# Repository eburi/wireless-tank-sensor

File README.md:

# 🚤 wireless-tank-sensor

A sealed, potted, maintenance-free **water tank level sensor** for boats (or caravans,
cabins, anything with a resistive tank sender and a 12 V bus). It runs on a
**Seeed XIAO ESP32-C3**, measures the plain old resistive float sender, works out the
level itself, and shouts the result at **Home Assistant** over **Bluetooth (BTHome v2)**.

You run **two wires** (12 V and ground) to the tank. That's it. No gauge, no Wi-Fi at
the tank, no app, no cloud. Everything else happens in the Home Assistant box you
already have on board.

> **TL;DR** — three ESPHome [external components](https://esphome.io/components/external_components/)
> (`bthome_beacon`, `tank_level`, `ota_beacon`) plus ready-to-copy example configs.
> Read on for the story, the wiring, and the lessons that cost me a night of sleep.

---

## 🧭 The backstory

When I bought the boat, she came with a set of tank sensors and a very confident
ship's manual. What she did *not* come with were the **analog gauges** those sensors
once fed — a previous owner had removed them at some point in the last geological era,
leaving behind a few dangling wires, a hole in the panel, and a gap in my
understanding of how much fresh water was actually left.

So for the first seasons the "fresh water level" was determined by a highly advanced
algorithm: *the pump starts sounding sad → tank is empty*. This works, in the sense
that a smoke alarm "works" as an oven timer.

Eventually I ripped out the corroded old senders and dropped in **cheap standard
resistive float senders** (~10 Ω to ~180 Ω, the kind every chandlery sells for the
price of a round of drinks). Then came the question: what to connect them to? Buying
new analog gauges felt like installing a fax machine. Buying a "smart" marine tank
monitor felt like paying for a fax machine with a subscription.

Meanwhile there was already a **Home Assistant** box on board, quietly collecting
temperatures, battery voltages and GPS fixes. It has Bluetooth. Bluetooth reaches the
tank locker. You can see where this is going.

The result is this repo: a tiny board that sits by the tank, needs only 12 V, sleeps
almost all the time, wakes up every ten seconds to measure the sender, and broadcasts
the level as a BTHome advertisement. Home Assistant picks it up like any other BTHome
gadget — no pairing, no integration to install, no IP address. The Wi-Fi radio is
switched off and only wakes for firmware updates, because on a boat the Wi-Fi is the
first thing you turn off to save power.

Now the fresh water tank shows up on the dashboard next to the batteries, the "tank
almost empty" sensor can nag me on my phone, and the pump has stopped sounding sad
unexpectedly. Mostly.

---

## ✨ What it does

| | |
|---|---|
| 📡 **BTHome v2 over BLE** | Home Assistant auto-discovers the sensor. Level (%), volume (L), raw sender resistance (Ω) and an *almost empty* problem flag, all in one 31-byte advertisement. |
| 😴 **Deep sleep duty cycle** | Wake → power the measurement chain → sample for ~2.5 s → advertise → sleep 10 s. The sender, the INA238 and its LED are completely unpowered in between. |
| 🧠 **Self-calibrating** | Learns the sender's real min/max resistance from the tank being filled and drained. Conservative: a new extreme needs five spaced observations, the least extreme one wins, the range never shrinks, spikes decay. Persisted to flash. |
| 🪣 **Tank content model** | Float senders have a dead zone at the bottom. Tell it total litres and how many litres the pump still delivers after the gauge reads 0 %, and it reports true content + a "you are now drinking the reserve" flag. Both numbers are editable in HA and stored on the device. |
| 🔒 **Wi-Fi off by default** | Turned on only in a 5-minute *maintenance window*: after a power cycle, or on request via a BLE trigger. If the boat Wi-Fi is gone, the node opens a fallback access point with a captive portal instead. |
| 🛰️ **BLE-triggered OTA** | A second ESP32 by the HA box advertises an iBeacon on demand (an HA switch). The sleeping sensor hears it on its next wake, opens Wi-Fi, and you flash it from the ESPHome dashboard. Potted in resin? Doesn't matter. |
| 🧱 **Fleet friendly** | One shared package, one ten-line file per tank, per-tank OTA targets, one API key for all. |
| 🔌 **Two wires** | 12 V in. Level out, through the air. |

---

## 🏗️ How it works

```mermaid
flowchart LR
    BUS[12 V bus] -->|PTC fuse, TVS, reverse diode| BUCK[buck module<br/>3.3 V]
    BUCK --> XIAO[XIAO ESP32-C3]
    XIAO <-->|I2C| INA[INA238<br/>current + voltage]
    RAIL[3.3 V] --> INA --> R2[series resistor] --> SENDER[float sender<br/>10–180 Ω] --> FET[logic-level MOSFET<br/>low-side switch] --> GND
    XIAO -->|GPIO3 MEAS_EN| FET
    XIAO -.->|BTHome adverts| HA[Home Assistant<br/>Bluetooth]
    BEACON[OTA trigger node<br/>second ESP32] -.->|iBeacon on demand| XIAO
    HA -->|switch| BEACON
```

The sender is just a variable resistor. The ESP switches a small current through it,
the INA238 measures that current and the voltage across the sender, and
`R = V / I`. No dependence on the supply rail, no dependence on the series resistor,
no ADC calibration. The `tank_level` component turns resistance into a percentage
using what it has learned about *your* sender, and `bthome_beacon` packs it into a
BTHome advertisement.

Because the node only listens for the OTA trigger while it is awake anyway, the
trigger costs nothing extra in power, and because it is a standard iBeacon frame
Home Assistant's iBeacon integration even shows the trigger as "present" while it is
on air — free proof the transmitter is transmitting.

---

## 🔩 Hardware

Two ways to build it. Both run the same firmware and the same example configs.

### Rev 3 — the carrier PCB (recommended)

A **55 × 52 mm four-layer carrier** in [hardware/kali-tank-sensor-v3/](hardware/kali-tank-sensor-v3/):
KiCad 10 project, DRC/ERC clean, gerbers, drill files, pick-and-place and BOM, ready for
a PCBWay-style order with SMT assembly. The XIAO and the buck module are hand-soldered
on top afterwards; four wire pads with strain-relief holes take the harness. See
[FABRICATION.md](hardware/kali-tank-sensor-v3/FABRICATION.md) for the order parameters,
assembly order and the things to check before first power-up.

| Part | Role | Approx. cost |
|------|------|-------------:|
| Seeed **XIAO ESP32-C3** + its **U.FL antenna** | Brain, BLE, deep sleep | €6 |
| **INA238** (bare MSOP-10, PCBWay places it) + **1 Ω 0.1 %** shunt | Measures chain current and sender voltage | €3 |
| **AO3400A** logic-level MOSFET | Low-side switch: sender is only powered while measuring | €0.10 |
| 100 Ω, 100 Ω, 100 kΩ, 2 × 4.7 kΩ | Current limit, gate series, gate pull-down, I2C pull-ups | pennies |
| 5–30 V → **3.3 V** buck module, 18 × 12 mm (mikroshop #2835 / DSN-MINI-360 class) | 12 V → 3.3 V | €1 |
| SS34, SMBJ16A, 200 mA PTC, 2 × 22 µF, 2 × 100 nF | Reverse-polarity, TVS, fuse, rail buffering | €1 |
| A resistive tank sender (any 10–180 Ω / 240–33 Ω / 0–190 Ω float sender) | The thing in the tank | €15–40 |

The whole thing runs on one 3.3 V rail: the buck feeds the XIAO's 3V3 pad through a
solder bridge (open it before plugging in USB), and the measurement chain runs from the
same rail through the INA238's own 1 Ω shunt. The I2C pull-ups hang on the switched
INA238 supply, so nothing back-feeds the chip while it sleeps unpowered.

### Rev 2 — the breadboard build

What ran on the bench and on the boat first: an INA238 *breakout* with its 15 mΩ shunt,
a BS170, a MINI-360 set to 5 V. Still valid, and the full wiring schema, part rationale,
bench findings and power budget for it live in [docs/hardware.md](docs/hardware.md).

| Part | Role | Approx. cost |
|------|------|-------------:|
| Seeed **XIAO ESP32-C3** + its **U.FL antenna** | Brain, BLE, deep sleep | €6 |
| **INA238** breakout (with onboard 15 mΩ shunt, I2C addr 0x40) | Measures chain current and sender voltage | €4 |
| **BS170** N-channel MOSFET | Low-side switch: sender is only powered while measuring | €0.20 |
| 150 Ω ¼ W, 100 Ω, 100 kΩ | Current limit, gate series, gate pull-down | pennies |
| **MINI-360** buck converter (set to 5.0 V) | 12 V → 5 V | €1 |
| 470 µF / 10 V, Schottky (1N5817), fuse | Rail buffering, USB back-feed protection, 12 V protection | €1 |

### XIAO pins (both revisions)

| XIAO pin | GPIO | Goes to |
|----------|------|---------|
| 3V3 (rev 3) / 5V (rev 2) | — | Supply from the buck; rev 3 via solder bridge SB1 |
| GND | — | Common ground |
| D1 | GPIO3 | MOSFET gate via 100 Ω (`MEAS_EN`) |
| D4 | GPIO6 | INA238 SDA |
| D5 | GPIO7 | INA238 SCL |
| D10 | GPIO10 | INA238 supply (`VS`, switched — the chip and its pull-ups are off in deep sleep) |

The sender must be **two-wire / isolated** (both terminals free) for the low-side
switch to work. A hull-grounded single-wire sender needs high-side switching instead —
adapt the FET stage, the firmware doesn't care.

---

## 🚀 Installing

You need ESPHome (the Home Assistant add-on is fine) and a Home Assistant with a
Bluetooth adapter or an ESPHome Bluetooth proxy in range of the tank.

### 1. Grab the example configs

Copy the [`examples/`](examples/) folder into your ESPHome config directory:

```
esphome/
  packages/tank-common.yaml     everything shared: sensors, INA238, tank_level, BTHome, HA numbers
  packages/tank-sleep.yaml      the sleep cycle + BLE trigger matcher (includes tank-common)
  water-tank-1.yaml             one device file per tank — copy it for tank 2, 3, …
  water-tank-bench.yaml         same hardware, Wi-Fi always on, no sleep: for first hookup
  ota-trigger-beacon.yaml       the trigger node (second ESP32, lives next to HA)
  secrets.yaml.example          copy to secrets.yaml and fill in
```

The components are pulled straight from this repo:

```yaml
external_components:
  - source: github://eburi/wireless-tank-sensor
    components: [bthome_beacon, tank_level]   # the trigger node uses [ota_beacon]
    refresh: 1d
```

Pin to a release for reproducible builds: `source: github://eburi/wireless-tank-sensor@v1.0.0`.

### 2. Name your tank

A device file is four lines of substitutions and one include:

```yaml
substitutions:
  device_name: water-tank-1       # ESPHome node name / hostname
  friendly_name: "Water Tank 1"   # prefix of every HA entity
  bthome_name: Tank1              # BLE local name, max 9 characters (the advert is full)
  ota_target: "1"                 # 1–255, unique per tank — which OTA trigger it answers to

packages:
  sleep: !include packages/tank-sleep.yaml
```

### 3. Check the sender direction

`tank_level` maps **low resistance = empty** by default. Many European / VDO-style
senders are the other way round (~10 Ω full, ~180 Ω empty). If your gauge goes down
while you fill, set `invert: true` in `packages/tank-common.yaml`. (Or just look at the
learned-range sensors while filling; it becomes obvious very quickly.)

### 4. Flash and forget

1. Flash **`water-tank-bench.yaml`** first, over USB. It keeps Wi-Fi on and the
   measurement chain powered, so you can watch *Sender resistance*, *Chain current*
   and *Sender voltage* live and confirm the wiring before you pot anything.
2. Once the numbers make sense, OTA-flash **`water-tank-1.yaml`**. From now on the
   node sleeps and only advertises over BLE.
3. Home Assistant → *Settings → Devices & Services* will offer a new **BTHome** device
   called `Tank1`. Accept it. Done.

### 5. Let it learn, then tell it about litres

Calibration happens by itself: fill the tank, empty the tank, repeat a couple of times
over the season. The learned range shows up as **Learned R min / max** and is saved to
flash, so it survives power cuts and firmware updates.

For real litres, do the **pump test** once: drain until the level reads its floor, then
count the litres the pump still delivers until it starts gasping. Enter that as
**Tank reserve volume** and the tank capacity as **Tank total volume** — two `number`
entities on the ESPHome device in HA (visible while the maintenance window is open; they
are stored on the ESP). From then on the level is true content and **Tank volume** reports
litres.

---

## 🏠 What shows up in Home Assistant

Via **BTHome** (always, over Bluetooth, no Wi-Fi involved):

| Entity | BTHome object | Meaning |
|--------|---------------|---------|
| `sensor.tank1_moisture` (HA may add a MAC suffix) | moisture (%) | Tank level. Yes, "moisture" — BTHome has no "tank level" object and moisture is a percentage. Rename it, nobody will know. |
| `sensor.tank1_volume` | volume (0.1 L) | Litres in the tank, once total/reserve are set |
| `sensor.tank1_count` | count (uint16) | Raw sender resistance × 10 (diagnostic; 1234 = 123.4 Ω) |
| `binary_sensor.tank1_problem` | problem | **Almost empty** — float on its bottom stop, you're drinking the reserve |

Via the **ESPHome native API** (only while Wi-Fi is on, i.e. in the maintenance window
or on the bench variant): the raw INA238 readings, *Sender resistance*, *Learned R min /
max*, the *Measurement path* and *INA238 power* switches, and the two litre `number`s.

---

## 🛰️ Updating firmware without touching the thing

The sensor is meant to be potted in resin inside a locker you never want to open
again, so it must be updatable without physical access — but it also keeps Wi-Fi off.
Two ways in:

- **Power cycle.** A cold boot always opens a **5-minute maintenance window**: Wi-Fi on,
  API on, continuous measurement. Flash from the ESPHome dashboard inside that window.
- **BLE trigger.** Flash a second ESP32 with [`ota-trigger-beacon.yaml`](examples/ota-trigger-beacon.yaml)
  and park it near the HA box. It exposes one HA switch per tank (**OTA trigger tank 1**,
  **… tank 2**, **… all tanks**). Turn one on: it advertises an iBeacon for 4 minutes,
  the matching sensor hears it on its next wake, opens its maintenance window, and you
  flash it. The switch turns itself off; a 6-minute firmware backstop makes sure the
  beacon never advertises forever (which would make every sensor open Wi-Fi on every
  wake — that's why ESPHome's built-in `esp32_ble_beacon` couldn't be used: it has no
  runtime off switch).

- **No Wi-Fi at all?** Every example carries a fallback **access point + captive portal**.
  If a node cannot join the configured Wi-Fi within a minute of switching the radio on, it
  opens a WPA2 access point named after the device (`water-tank-1`, …), protected by
  `wifi_ap_password` from `secrets.yaml`. Join it, and the captive
  portal lets you enter new credentials or upload a firmware file — still no screwdriver.

> **Why not transmit from the HA host's own Bluetooth?** Tried it. On Home Assistant OS
> the Bluetooth integration owns the adapters and BlueZ refuses to register an
> advertisement (`org.bluez.Error.Failed`), even on an idle second adapter. A €6 ESP32 is
> cheaper than fighting BlueZ, and it doubles as a Bluetooth proxy.

> **The trigger format is a contract between two firmwares.** If you change the UUID,
> major or minor, reflash *both* ends. A sensor on an old build silently ignores the new
> trigger, and you will spend an evening wondering why. Ask me how I know.

---

## 🧪 The components

All three are plain ESPHome external components under [`components/`](components/).

### `bthome_beacon`

Non-connectable BLE advertiser producing a BTHome v2 service-data frame (UUID `0xFCD2`).
Objects are emitted in ascending id order as BTHome requires: packet id, `almost_empty`
(problem, `0x26`), `level` (moisture, `0x2F`), `count` (`0x3D`, value × 10), `volume`
(`0x47`, 0.1 L). Re-advertises once per second with the current sensor states.

```yaml
bthome_beacon:
  device_name: "Tank1"          # ≤ 9 chars if all four objects are used
  level: tank_level_cal         # sensor, % (required)
  count: sender_resistance      # sensor, × 10 → uint16 (optional)
  volume: tank_volume           # sensor, L (optional)
  almost_empty: tank_almost_empty   # binary_sensor (optional)
```

### `tank_level`

Resistance in, level out. Median-of-5 input window (kept in RTC memory so it spans
wake cycles), conservative learned min/max with NVS persistence that only ever learns
from a full-window median, EMA smoothing across deep-sleep cycles, and implausible
readings (outside `plausible_min`/`plausible_max`, NaN) hold the last good level
instead of publishing garbage. Optional volume model.

```yaml
tank_level:
  id: tank_model
  source: sender_resistance     # raw Ω sensor
  seed_min: 3.0                 # assumed range until enough is learned
  seed_max: 183.0
  invert: false                 # true if low resistance = full
  plausible_max: 250            # Ω; readings above are faults (default 400)
  level: { name: "Tank level" }
  volume: { name: "Tank volume" }
  almost_empty: { name: "Tank almost empty" }
  learned_min: { name: "Learned R min" }
  learned_max: { name: "Learned R max" }
```

Runtime setters `set_total_volume(l)` / `set_reserve_volume(l)` are what the two HA
`number` entities in the example call, and `reset_calibration()` is behind the
**Reset calibration** button: the learned range never shrinks on its own, so press it
after swapping the sender or whenever a bad range got in, then move the float through
its full travel a few times.

### `ota_beacon`

iBeacon transmitter with a runtime on/off and a safety timeout. Fixed major `0x4B4F`
("KO"), minor `0x54<target>` ("T" + tank number, 0 = all tanks). The sensor matches on
major/minor because those are byte-order unambiguous in ESPHome's iBeacon parser; the
UUID is only for Home Assistant's iBeacon integration to display.

```yaml
ota_beacon:
  id: trigger
  uuid: c0a1b2c3-d4e5-4f60-8172-8394a5b6c7d8
  safety_timeout: 6min
# then from a switch/automation:  id(trigger).start(1);  id(trigger).stop();
```

---

## 🧯 Lessons learned (so you don't have to)

- **The XIAO ESP32-C3 has no on-board antenna.** None. The U.FL pigtail is not optional.
  Without it the radio still "works" at bench range — BTHome reached a Raspberry Pi two
  metres away at −98 dBm, one dB above the noise floor — which is exactly why it went
  unnoticed while I debugged the OTA trigger firmware on *both* ends for a whole night.
  Attaching the antenna took the signal to a healthy −75 dBm. Glue the antenna down
  before potting; the connector pops off.
- **Check your MOSFET pinout with a meter.** My batch of "BS170"s had a mirrored
  S-G-D pinout. Installed per datasheet they conduct permanently through the body diode.
  The *path-off ≈ 0 mA* check on the bench catches this in ten seconds.
- **INA238 conversion time must fit the update interval.** `adc_time × averaging × 3
  channels` longer than `update_interval` means ESPHome's driver restarts the conversion
  every cycle and never publishes a value. 1052 µs × 128 at 1 s works; 4120 µs × 128
  does not.
- **The breakout's I2C pull-ups ride on its VIN.** At 5 V they idle at 5 V, which the
  ESP32-C3 does not appreciate. Feeding the breakout's VIN from a 3.3 V GPIO fixes the
  levels *and* makes the whole breakout (LED included) switch off in deep sleep for free.
- **Float senders have a dead zone.** The float bottoms out with litres still in the
  tank. Measure it once with the pump, tell the firmware, and stop lying to yourself
  about "0 %".
- **The first sample after switching the sender on is a lie.** The INA238 converts bus
  voltage and shunt current one after the other. Switch the measurement path on between
  the two and you get the resting rail voltage divided by the real current: sender plus
  about 130 Ω. On a sleeping node that happens at the same instant every wake, and the
  calibration happily learned 300 Ω as "full" from five of those. Hence the two-second
  settle gate in the example config, the full-window rule in `tank_level`, and the
  `plausible_max` option.
- **Verify a module's pad map against a photo of its bottom face, not its silkscreen
  logic.** The first carrier footprint grouped the buck's four corner pads by polarity
  (IN+ and IN− at opposite ends). The real module groups them by side: the long pitch
  separates IN from OUT, the short pitch separates + from −. Built as drawn it would have
  put 12 V backwards across the input and shorted the output to ground. Two photos and a
  meter, before ordering, are cheaper than five dead boards.
- **The first board layout is a third empty.** Rev 3.0 came out at 80 × 55 mm because the
  input chain and the buck formed one long row with the MCU beside it. Stacking the buck
  over the MCU and moving the analog block next to the wire pads gave 55 × 52 mm with the
  same circuit and shorter sender traces. Look at the empty regions before you order.
- **A 31-byte advertisement fills up fast.** Four BTHome objects plus a name leave nine
  characters for the name. Keep it short.

---

## 🗂️ Repo layout

```
components/
  bthome_beacon/    BTHome v2 advertiser
  tank_level/       self-calibrating level + volume model
  ota_beacon/       switchable iBeacon OTA trigger
examples/           ready-to-copy ESPHome configs (see Installing)
hardware/
  kali-tank-sensor-v3/  rev 3 carrier PCB: KiCad 10 project, gen_sch.py / gen_pcb.py
                        (the board is generated from source), gerbers + drill + CPL + BOM,
                        FABRICATION.md with order parameters and pre-power-up checks
docs/
  hardware.md       full hardware plan, wiring, rationale, bench notes, power budget
  wiring-schema.svg
  concept.md        the original design brief
.github/workflows/  CI compiles every example against the components in the repo
```

---

## 🤝 Contributing

Issues and PRs welcome — especially reports of other senders, other boards, or a
cleverer way to get litres out of a float. If you build one, I'd love a photo of your
tank locker. Fair winds.

## 📜 License

[MIT](LICENSE). Built for the sailing yacht *Kali*; no boats were harmed in the making
of this firmware, though one MOSFET was.

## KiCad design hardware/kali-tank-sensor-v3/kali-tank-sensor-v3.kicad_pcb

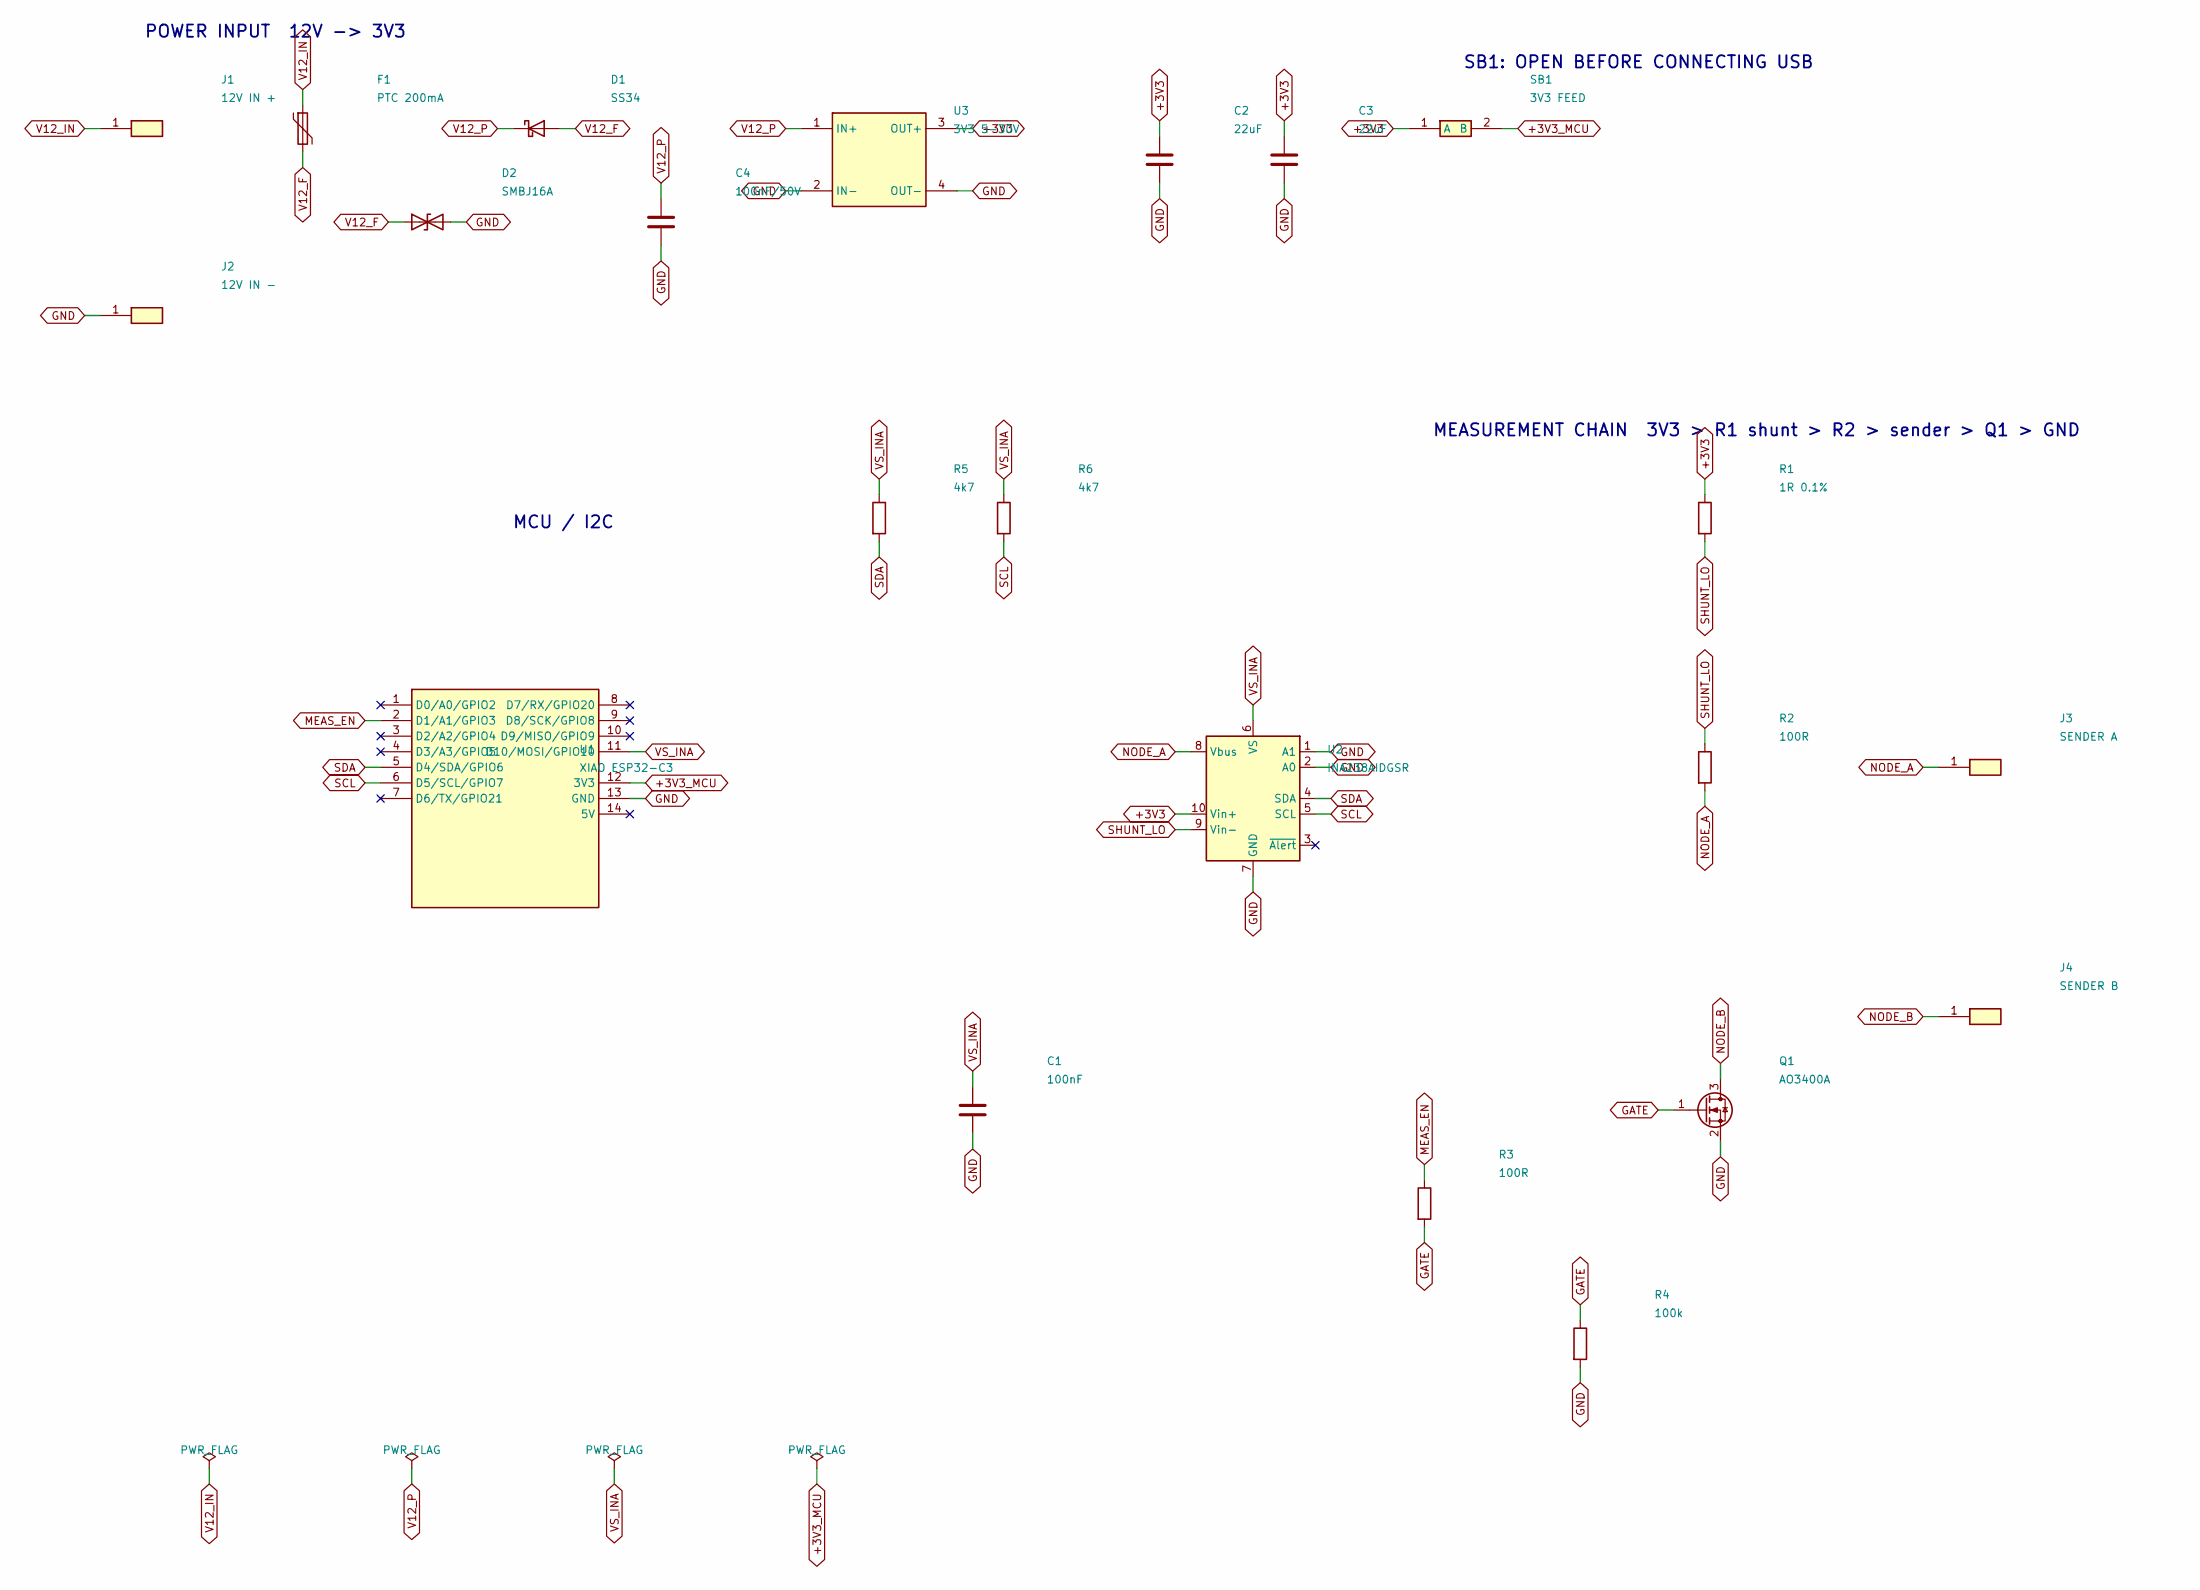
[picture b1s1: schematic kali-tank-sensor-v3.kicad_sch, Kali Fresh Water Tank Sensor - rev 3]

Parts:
C1: 100nF; C_0805_2012Metric
C2, C3: 22uF; C_1206_3216Metric
C4: 100nF/50V; C_0805_2012Metric
D1: SS34; D_SMA
D2: SMBJ16A; D_SMB
F1: PTC 200mA; R_1206_3216Metric
J1: 12V IN +; WirePad_StrainRelief
J2: 12V IN -; WirePad_StrainRelief
J3: SENDER A; WirePad_StrainRelief
J4: SENDER B; WirePad_StrainRelief
Q1: AO3400A; SOT-23
R1: 1R 0.1%; R_0805_2012Metric
R2, R3: 100R; R_0805_2012Metric
R4: 100k; R_0805_2012Metric
R5, R6: 4k7; R_0805_2012Metric
SB1: 3V3 FEED; SolderBridge_2pad
U1: XIAO ESP32-C3; XIAO-ESP32C3_TopSolder
U2: INA238AIDGSR; MSOP-10_3x3mm_P0.5mm
U3: 3V3 5-30V; DCDC_Module_18x12_4pad

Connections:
+3V3: C2.1, C3.1, R1.1, SB1.1 (A), U2.10 (Vin+), U3.3 (OUT+)
+3V3_MCU: SB1.2 (B), U1.12 (3V3)
GATE: Q1.1 (G), R3.2, R4.1
GND: C1.2, C2.2, C3.2, C4.2, D2.2 (A2), J2.1, Q1.2 (S), R4.2, U1.13 (GND), U2.1 (A1), U2.2 (A0), U2.7 (GND), U3.2 (IN-), U3.4 (OUT-)
MEAS_EN: R3.1, U1.2 (D1/A1/GPIO3)
NODE_A: J3.1, R2.2, U2.8 (Vbus)
NODE_B: J4.1, Q1.3 (D)
SCL: R6.2, U1.6 (D5/SCL/GPIO7), U2.5 (SCL)
SDA: R5.2, U1.5 (D4/SDA/GPIO6), U2.4 (SDA)
SHUNT_LO: R1.2, R2.1, U2.9 (Vin-)
V12_F: D1.2 (A), D2.1 (A1), F1.2
V12_IN: F1.1, J1.1
V12_P: C4.1, D1.1 (K), U3.1 (IN+)
VS_INA: C1.1, R5.1, R6.1, U1.11 (D10/MOSI/GPIO10), U2.6 (VS)

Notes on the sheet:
POWER INPUT 12V -> 3V3
MEASUREMENT CHAIN 3V3 > R1 shunt > R2 > sender > Q1 > GND
MCU / I2C
SB1: OPEN BEFORE CONNECTING USB

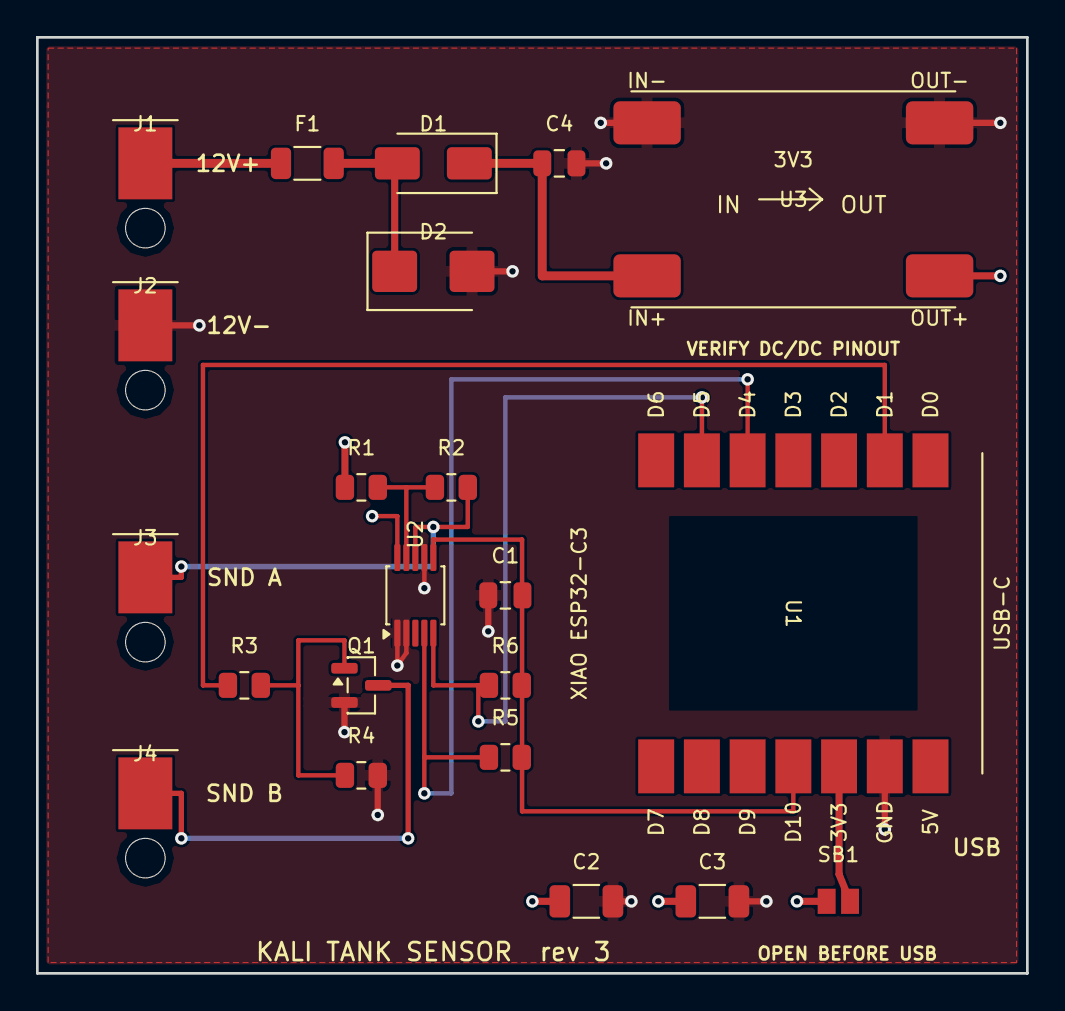
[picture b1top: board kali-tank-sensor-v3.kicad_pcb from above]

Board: 4 copper layers, 55.0 x 52.0 mm, 22 parts (0 on the bottom side), 14 nets.

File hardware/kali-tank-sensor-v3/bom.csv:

Reference,Qty,Value,Footprint,Manufacturer PN,Source,Notes
U1,1,Seeed XIAO ESP32-C3,kali:XIAO-ESP32C3_TopSolder,113991054,Seeed,HAND-SOLDER after delivery. Flash BEFORE soldering down.
U2,1,INA238AIDGSR,Package_SO:MSOP-10_3x3mm_P0.5mm,INA238AIDGSR,LCSC C2868250 / DigiKey,PCBWay places. Consign to avoid markup.
U3,1,3.3V buck 5-30V 3A,kali:DCDC_Module_18x12_4pad,mikroshop 2835,mikroshop.ch,HAND-SOLDER. VERIFY CORNER PINOUT FIRST.
R1,1,1R 0.1% 25ppm,Resistor_SMD:R_0805_2012Metric,,,Current-sense shunt. Precision matters here.
R2,1,100R 1%,Resistor_SMD:R_0805_2012Metric,,,Chain current limit
R3,1,100R,Resistor_SMD:R_0805_2012Metric,,,Q1 gate series
R4,1,100k,Resistor_SMD:R_0805_2012Metric,,,Q1 gate pull-down (holds path off in sleep)
R5,1,4k7,Resistor_SMD:R_0805_2012Metric,,,SDA pull-up to VS_INA (switched)
R6,1,4k7,Resistor_SMD:R_0805_2012Metric,,,SCL pull-up to VS_INA (switched)
C1,1,100nF X7R 16V,Capacitor_SMD:C_0805_2012Metric,,,INA238 VS decoupling
C2,1,22uF X5R 10V,Capacitor_SMD:C_1206_3216Metric,,,3V3 bulk at the regulator
C3,1,22uF X5R 10V,Capacitor_SMD:C_1206_3216Metric,,,3V3 bulk at the MCU (BLE TX bursts)
C4,1,100nF X7R 50V,Capacitor_SMD:C_0805_2012Metric,,,12V input HF decoupling
D1,1,SS34,Diode_SMD:D_SMA,SS34,,Reverse-polarity block. 40V > TVS clamp.
D2,1,SMBJ16A,Diode_SMD:D_SMB,SMBJ16A,,"TVS, 26.0V clamp. NOT SMBJ18A - 29.2V is too close to the module's 30V max."
F1,1,PTC 200mA hold,Resistor_SMD:R_1206_3216Metric,,,Fuses the TVS failure mode (TVS fails short)
Q1,1,AO3400A,Package_TO_SOT_SMD:SOT-23,AO3400A,,"Logic-level. NOT BS170/2N7002 - marginal at 3.3V gate."
SB1,1,Solder bridge,kali:SolderBridge_2pad,,,"Normally CLOSED. OPEN before connecting USB."
J1-J4,4,Wire pad,kali:WirePad_StrainRelief,,,"Solder pads, 2.2mm strain-relief hole below each"
